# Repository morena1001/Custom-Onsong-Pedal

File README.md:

# Custom Onsong Pedal
A custom keyboard based pedal for Onsong, 
a songbook application used for organizing 
songs. 

Onsong is a songbook app with the ability 
to customize chords, add capo,  and create
sets or playlists. This app also supports 
pedals to be able to change songs, chords, 
etc. handsfree. They offer their own pedals, 
or a custom keyboard based pedal with support for at most 8 different characters that converts keyboard presses into inputs. This project
implements a custom keyboard pedal for use in live performances.

This pedal was developed to solve an issue I was having. I am part of my church's worship team, and changing the song or scrolling through them forces me to take a hand away from the piano. By having foot pedals to control those actions, I can keep playing while keeping up with the current song.

This project uses the [ESP32 BLE Keyboard library](https://github.com/T-vK/ESP32-BLE-Keyboard), which handles BLE communication and transmission of keystrokes. The software uses a simple for loop that continuously checks for button presses and makes use of a software debounce to filter out acidental presses or interference. 

Hardware wise, the project uses the [HiLetgo ESP-WROOM-32S](https://www.amazon.com/dp/B0718T232Z?ref=ppx_yo2ov_dt_b_fed_asin_title&th=1), a USB-C, 5V 2A boost converter with lithium battery charging protection board, and a 3.7V, 1600mAh Li-Po battery. This setup provides the pedals with enough power to last several worship services on a single charge. 

The design for the pedals take on a modular approach. Each button or pedal has its own individual case, and when connected via magnetic pogo connectors to either the main pedal that houses all of the hardware components, or the chain of pedals already connected to the main pedal, power is provided to that pedal and it can then transmit its associated character.

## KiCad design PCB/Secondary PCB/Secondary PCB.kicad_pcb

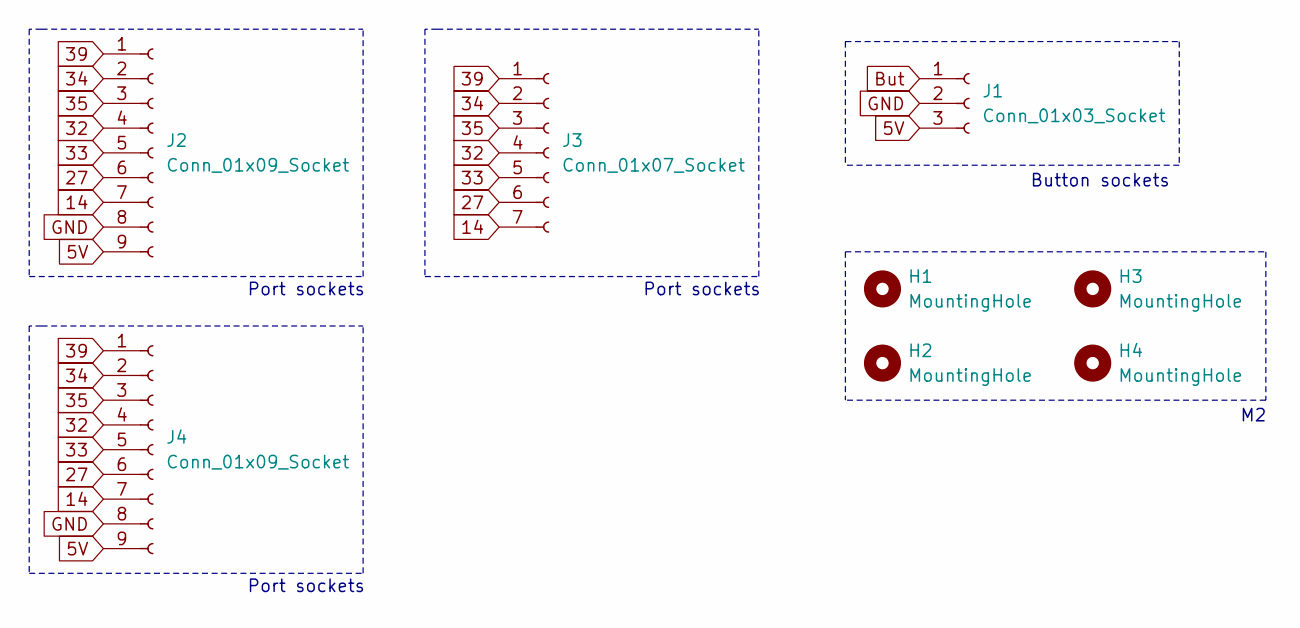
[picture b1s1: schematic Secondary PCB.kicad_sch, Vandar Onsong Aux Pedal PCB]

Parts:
H1, H2, H3, H4: MountingHole; MountingHole_2.2mm_M2
J1: Conn_01x03_Socket; PinHeader_1x03_P2.54mm_Vertical
J2, J4: Conn_01x09_Socket; PinHeader_1x09_P2.54mm_Vertical
J3: Conn_01x07_Socket; PinHeader_1x07_P2.54mm_Vertical

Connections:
5V: J1.3, J2.9, J4.9
14: J2.7, J3.7, J4.7
27: J2.6, J3.6, J4.6
32: J2.4, J3.4, J4.4
33: J2.5, J3.5, J4.5
34: J2.2, J3.2, J4.2
35: J2.3, J3.3, J4.3
39: J2.1, J3.1, J4.1
But: J1.1
GND: J1.2, J2.8, J4.8

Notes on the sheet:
Button sockets
Port sockets

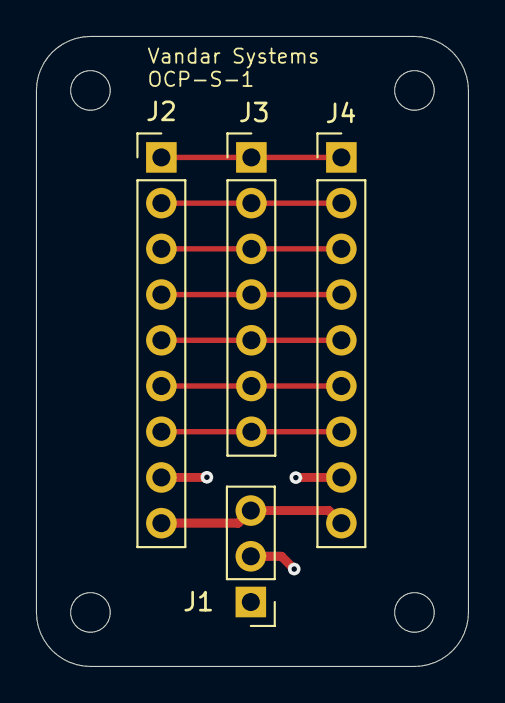
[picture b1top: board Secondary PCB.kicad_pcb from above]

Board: 2 copper layers, 24.0 x 35.0 mm, 8 parts (0 on the bottom side), 9 nets.

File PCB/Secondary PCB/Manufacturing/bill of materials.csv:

"Reference","Value","Datasheet","Footprint","Qty","DNP"
"J1","Conn_01x03_Socket","~","Connector_PinHeader_2.54mm:PinHeader_1x03_P2.54mm_Vertical","1",""
"J2,J4","Conn_01x09_Socket","~","Connector_PinHeader_2.54mm:PinHeader_1x09_P2.54mm_Vertical","2",""
"J3","Conn_01x07_Socket","~","Connector_PinHeader_2.54mm:PinHeader_1x07_P2.54mm_Vertical","1",""

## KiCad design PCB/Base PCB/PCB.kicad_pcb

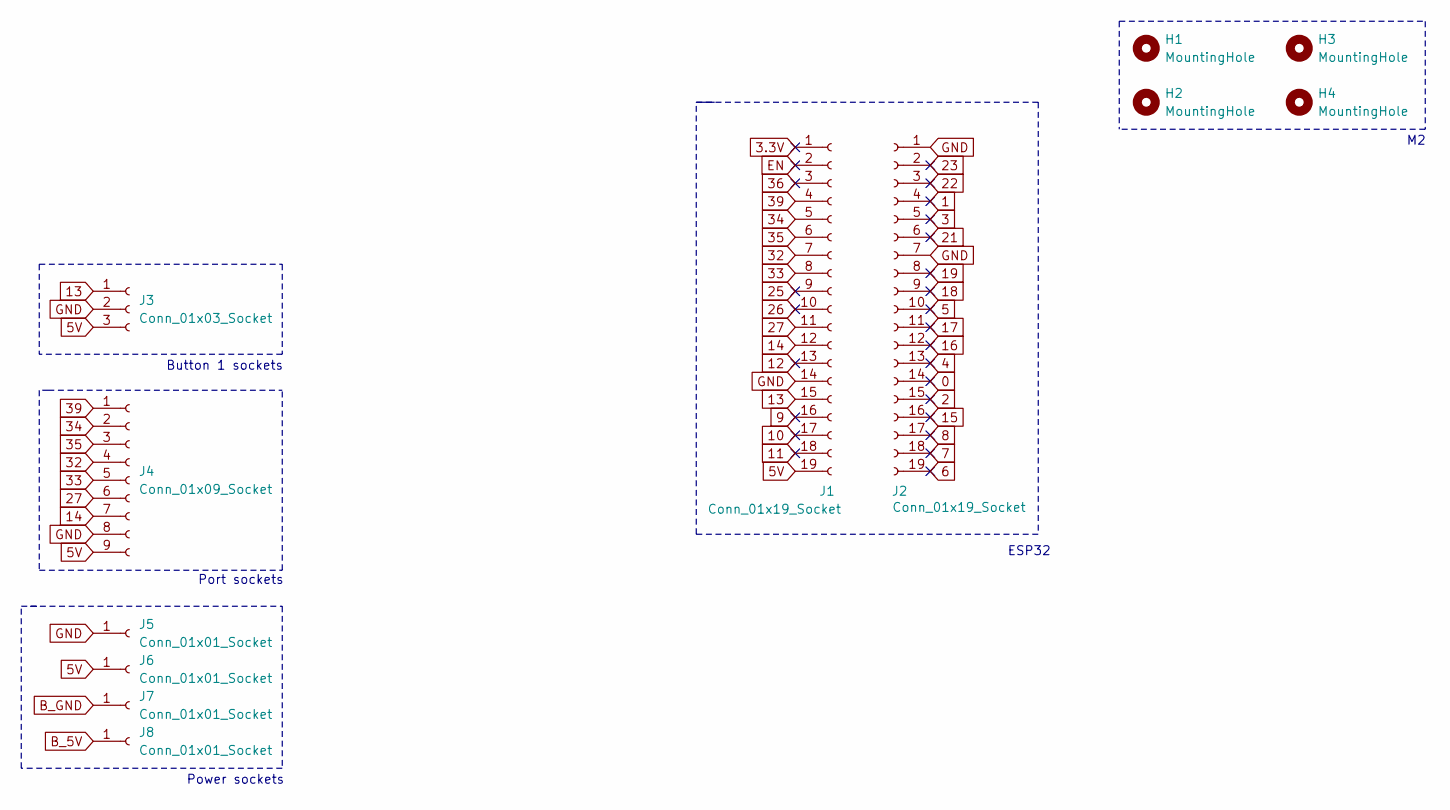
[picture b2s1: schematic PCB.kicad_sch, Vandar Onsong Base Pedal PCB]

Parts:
H1, H2, H3, H4: MountingHole; MountingHole_2.2mm_M2
J1, J2: Conn_01x19_Socket; PinHeader_1x19_P2.54mm_Vertical
J3: Conn_01x03_Socket; PinHeader_1x03_P2.54mm_Vertical
J4: Conn_01x09_Socket; PinHeader_1x09_P2.54mm_Vertical
J5, J6, J7, J8: Conn_01x01_Socket; PinHeader_1x01_P2.54mm_Vertical

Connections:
0: J2.14
1: J2.4
2: J2.15
3: J2.5
3.3V: J1.1
4: J2.13
5: J2.10
5V: J1.19, J3.3, J4.9, J6.1
6: J2.19
7: J2.18
8: J2.17
9: J1.16
10: J1.17
11: J1.18
12: J1.13
13: J1.15, J3.1
14: J1.12, J4.7
15: J2.16
16: J2.12
17: J2.11
18: J2.9
19: J2.8
21: J2.6
22: J2.3
23: J2.2
25: J1.9
26: J1.10
27: J1.11, J4.6
32: J1.7, J4.4
33: J1.8, J4.5
34: J1.5, J4.2
35: J1.6, J4.3
36: J1.3
39: J1.4, J4.1
B_5V: J8.1
B_GND: J7.1
EN: J1.2
GND: J1.14, J2.1, J2.7, J3.2, J4.8, J5.1

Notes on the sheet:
Power sockets
ESP32
Port sockets
Button 1 sockets

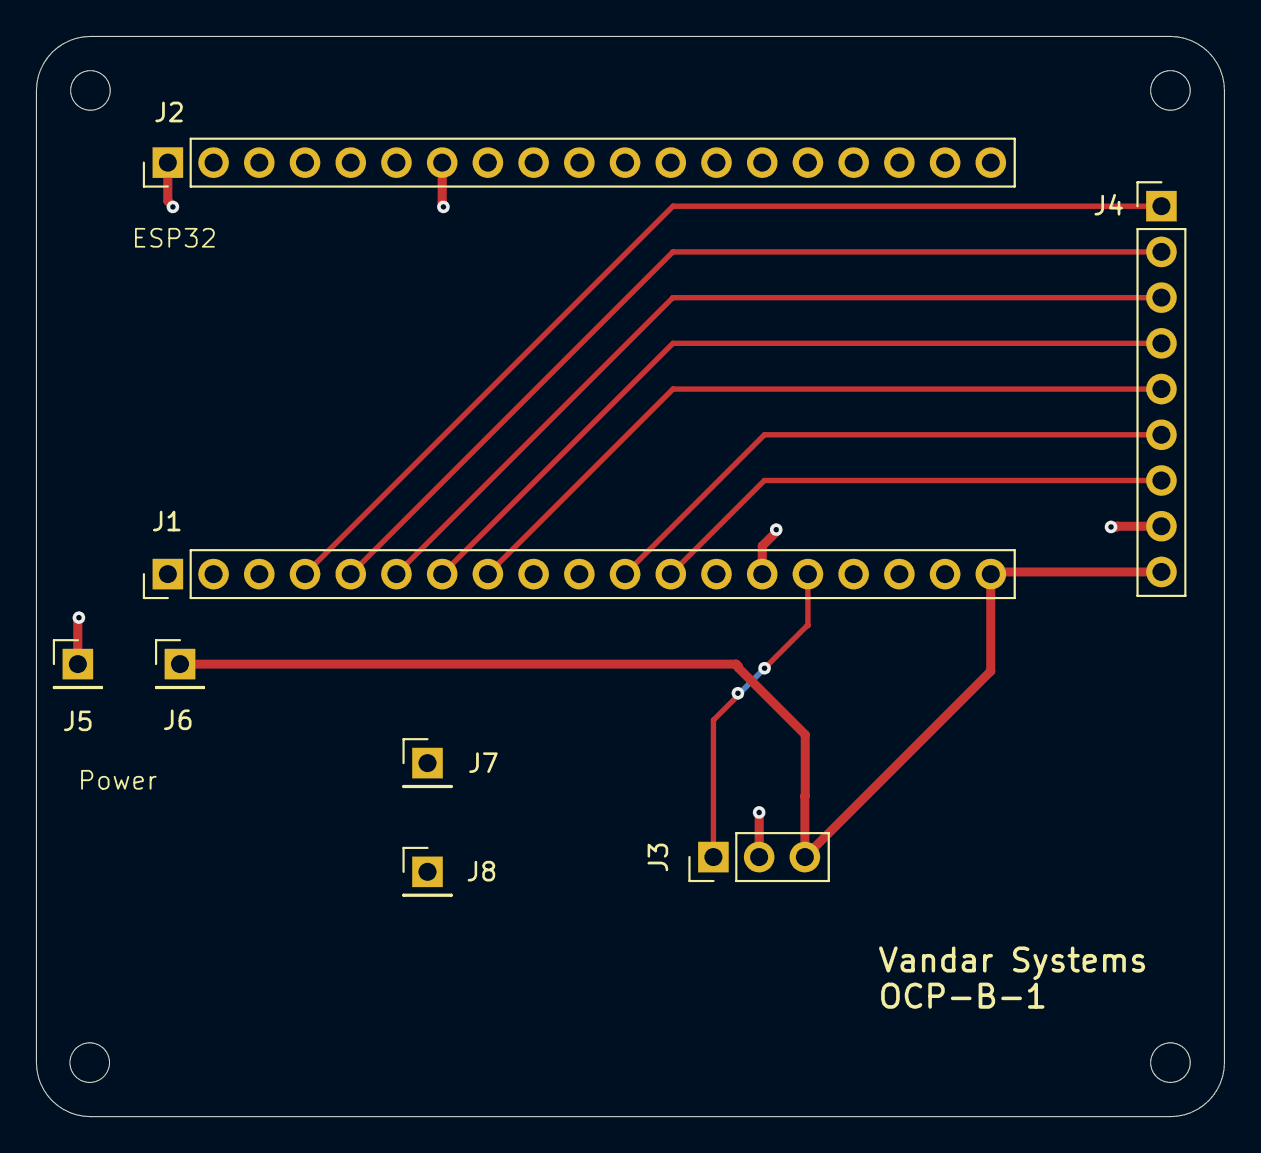
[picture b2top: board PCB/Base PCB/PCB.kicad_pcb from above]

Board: 2 copper layers, 66.0 x 60.0 mm, 12 parts (0 on the bottom side), 10 nets.

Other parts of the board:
H2#2: MountingHole; MountingHole_2.2mm_M2

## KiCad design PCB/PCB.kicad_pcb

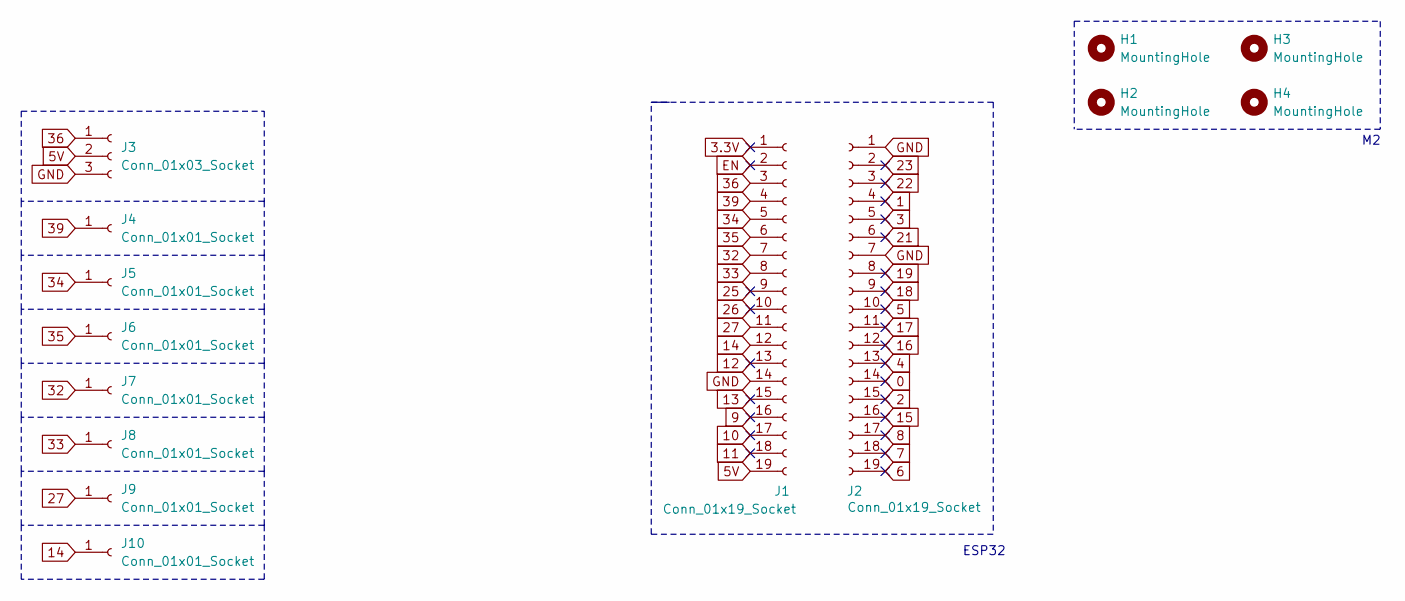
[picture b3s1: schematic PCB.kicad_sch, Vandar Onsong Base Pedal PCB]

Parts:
H1, H2, H3, H4: MountingHole; MountingHole_2.2mm_M2
J1, J2: Conn_01x19_Socket; PinHeader_1x19_P2.54mm_Vertical
J3: Conn_01x03_Socket; PinHeader_1x03_P2.54mm_Vertical
J4, J5, J6, J7, J8, J9, J10: Conn_01x01_Socket; PinHeader_1x01_P2.54mm_Vertical

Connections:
0: J2.14
1: J2.4
2: J2.15
3: J2.5
3.3V: J1.1
4: J2.13
5: J2.10
5V: J1.19, J3.2
6: J2.19
7: J2.18
8: J2.17
9: J1.16
10: J1.17
11: J1.18
12: J1.13
13: J1.15
14: J1.12, J10.1
15: J2.16
16: J2.12
17: J2.11
18: J2.9
19: J2.8
21: J2.6
22: J2.3
23: J2.2
25: J1.9
26: J1.10
27: J1.11, J9.1
32: J1.7, J7.1
33: J1.8, J8.1
34: J1.5, J5.1
35: J1.6, J6.1
36: J1.3, J3.1
39: J1.4, J4.1
EN: J1.2
GND: J1.14, J2.1, J2.7, J3.3

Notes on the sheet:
ESP32

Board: 2 copper layers, 14 parts (0 on the bottom side), 10 nets, no tracks yet.

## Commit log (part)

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2025-12-25 Create Thoughts
2025-12-25 Rename Thoughts to Thoughts.md
2025-12-26 Added folders to store the project files at different stages of the project. I think I can already start working on the simulation
2025-12-27 Skipped simulation because I had already developed demo before. It works, but now need to test that all of the buttons work, and mess with the input I want to use to see what I'd like to use for my f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
2025-12-27 Fixed some errors and made sure that the code works. I think I can even connect to the foot pedal via the iPad's settings page, which I think removes the need for the 3rd party BLE app. Next I want t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
2026-01-04 Added new files for the PCB, had to stop because I decided to change they layout of the pedals. Need to finish the pogo pin ports, and research more about what kind of battery will better suit my nee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
2026-01-26 Finished the rough draft for the enclosure. I used the 3d models from KiCad to get the PCB dimensions.
2026-01-26 updated files
2026-01-27 Made updates to case files
